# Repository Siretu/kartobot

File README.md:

# kartobot

### Introduction
This project was created by [@Siretu](https://github.com/user/Siretu), [@setfal](https://github.com/user/setfal) and [@exuvo](https://github.com/user/exuvo) as a project course. We built and programmed a navigation robot pretty much from scratch. The robot (called kartobot) is equipped with a tower of two rotating ultrasonic sensors. These rotate continuously to provide the robot with sensor input about its surroundings. This data is then sent to the computer wirelessly using the xbee chip. The navigation data is drawn as a map on the computer and it's also used locally on the robot to avoid obstacles. The robot uses a dynamic A* pathfinding to automatically explore more of the surrounding areas.

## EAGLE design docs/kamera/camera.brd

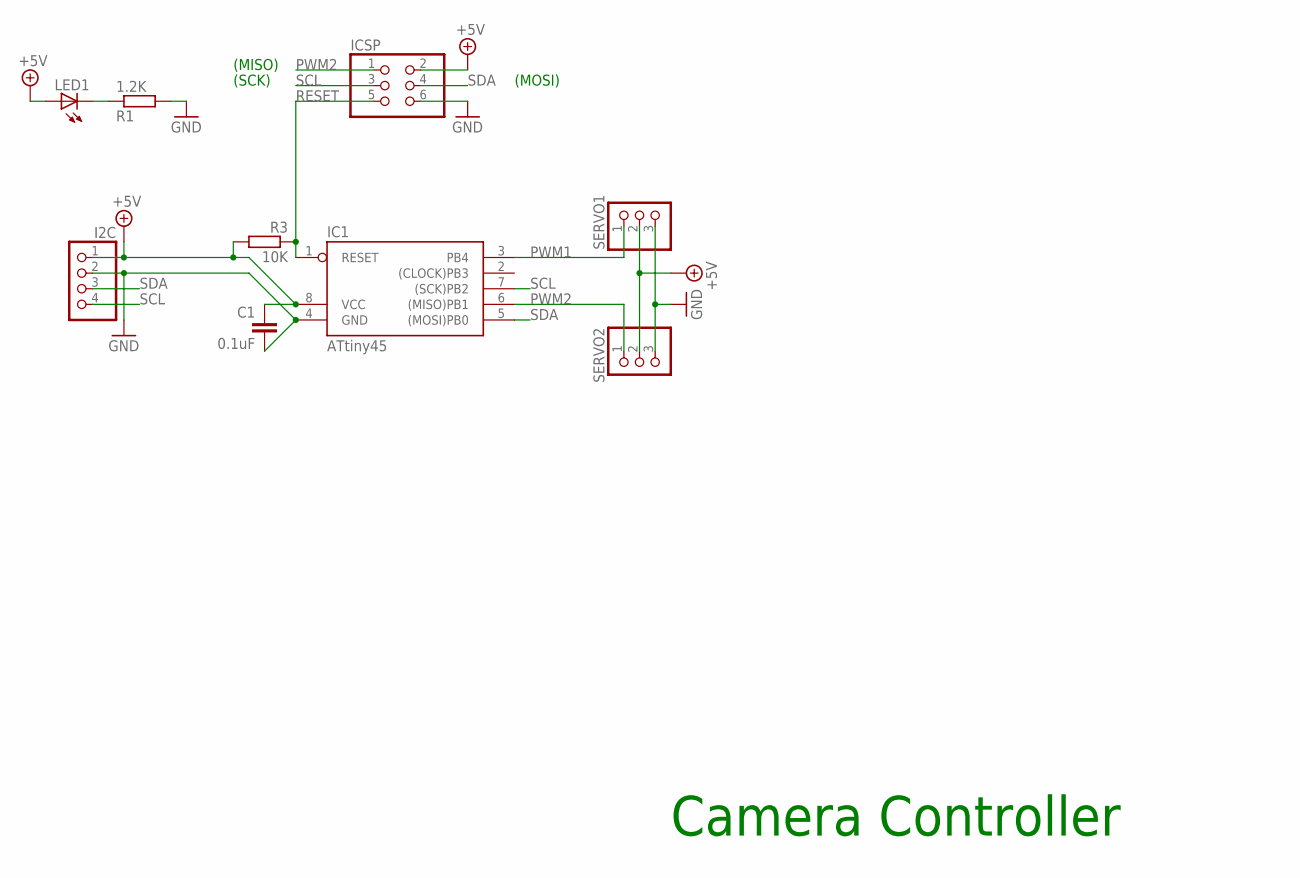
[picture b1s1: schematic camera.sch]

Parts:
C1: 0.1uF; C025-024X044
I2C: PINHD-1X4; 1X04
IC1: ATtiny45; DIL08
ICSP: PINHD-2X3; 2X03
LED1: LED5MM
R1: 1.2K; 0207/2V
R3: 10K; 0207/2V
SERVO1, SERVO2: PINHD-1X3; 1X03

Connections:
+5V: C1.1, I2C.1, IC1.8 (VCC), ICSP.2, LED1.A, R3.2, SERVO1.2, SERVO2.2
GND: C1.2, I2C.2, IC1.4 (GND), ICSP.6, R1.2, SERVO1.3, SERVO2.3
unnamed: LED1.K (C), R1.1
PWM1: IC1.3 (PB4), SERVO1.1
PWM2: IC1.6 ((MISO)PB1), ICSP.1, SERVO2.1
RESET: IC1.1 (RESET), ICSP.5, R3.1
SCL: I2C.4, IC1.7 ((SCK)PB2), ICSP.3
SDA: I2C.3, IC1.5 ((MOSI)PB0), ICSP.4

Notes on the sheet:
(SCK)
(MOSI)
(MISO)
Camera Controller

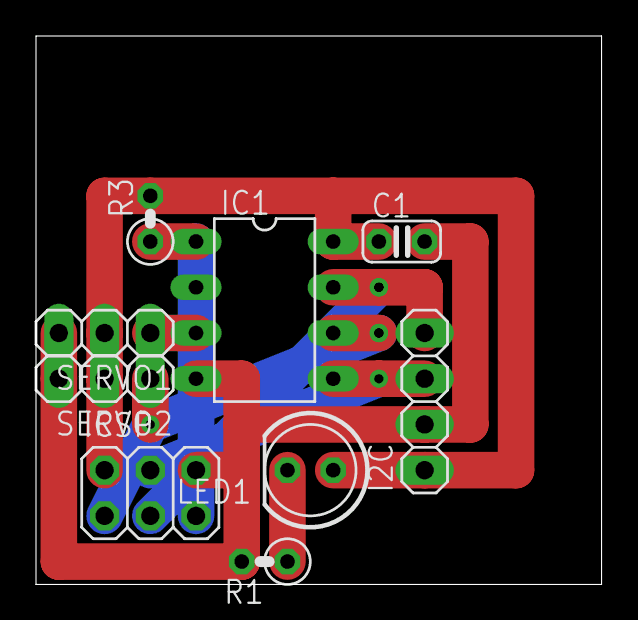
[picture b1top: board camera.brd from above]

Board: 2 copper layers, 31.4 x 30.5 mm, 9 parts (0 on the bottom side), 8 nets.

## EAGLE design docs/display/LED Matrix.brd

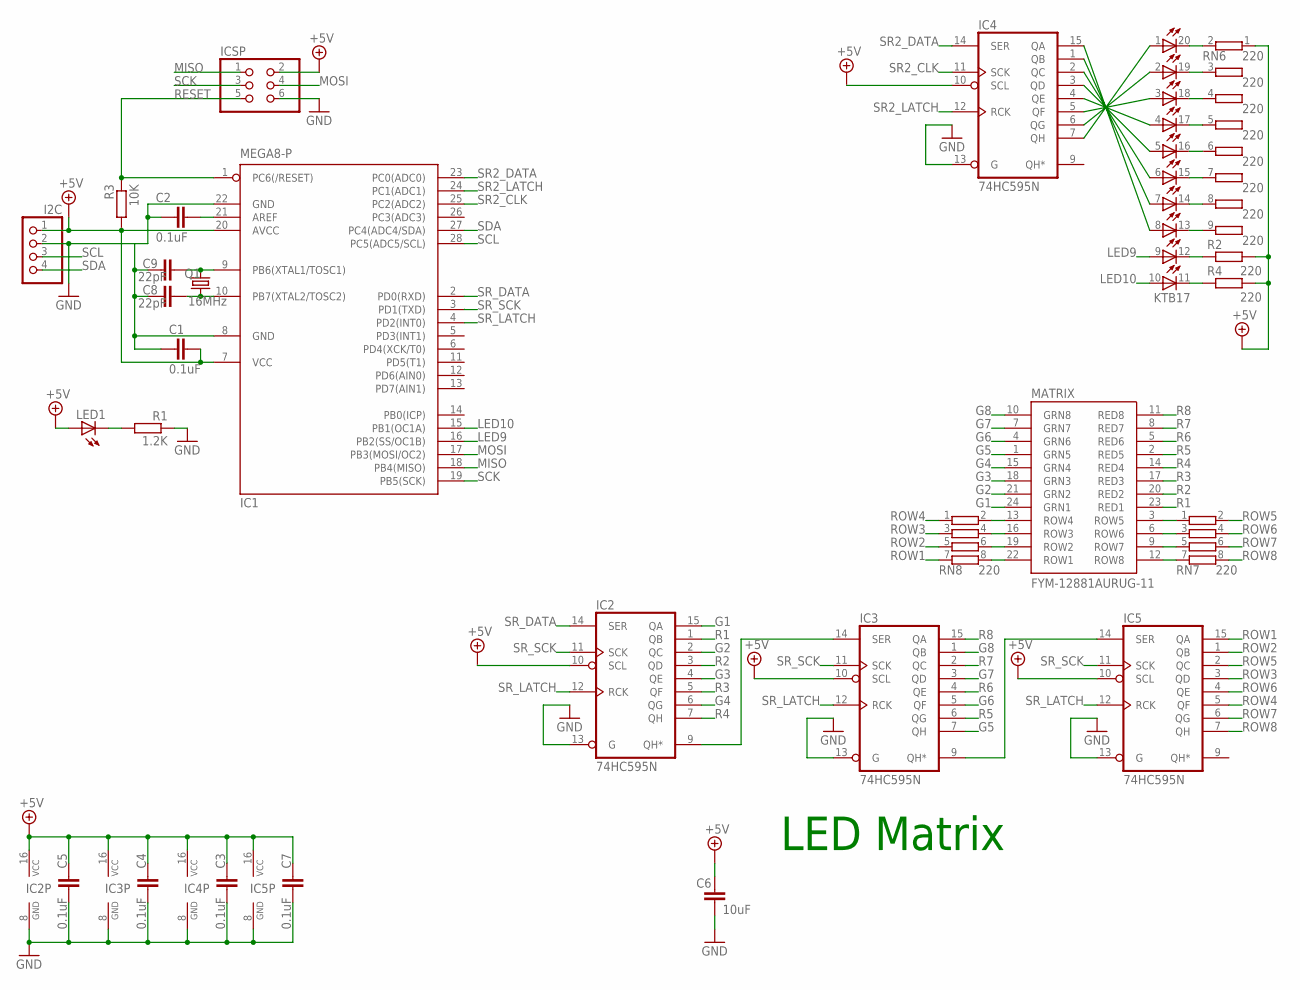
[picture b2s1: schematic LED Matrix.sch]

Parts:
-: KTB17; LB10
C1, C2, C3, C4, C5, C7: 0.1uF; C025-024X044
C6: 10uF; C025-024X044
C8, C9: 22pF; C025-024X044
I2C: PINHD-1X4; 1X04
IC1: MEGA8-P; DIL28-3
IC2, IC3, IC4, IC5: 74HC595N; DIL16
ICSP: PINHD-2X3; 2X03
LED1: LED5MM
MATRIX: FYM-12881AURUG-11; YSM-1288CR3G2C
Q1: 16MHz; HC49/S
R1: 1.2K; 0207/2V
R2, R4: 220; 0207/2V
R3: 10K; 0207/2V
RN6: 220; SIL9
RN7, RN8: 220; SIL8

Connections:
+5V: C1.2, C3.1, C4.1, C5.1, C6.1, C7.1, I2C.1, IC1.7 (VCC), IC1.20 (AVCC), IC2.10 (SCL), IC2.16 (VCC), IC3.10 (SCL), IC3.16 (VCC), IC4.10 (SCL), IC4.16 (VCC), IC5.10 (SCL), IC5.16 (VCC), ICSP.2, LED1.A, R2.2, R3.2, R4.2, RN6.1
G1: IC2.15 (QA), MATRIX.24 (GRN1)
G2: IC2.2 (QC), MATRIX.21 (GRN2)
G3: IC2.4 (QE), MATRIX.18 (GRN3)
G4: IC2.6 (QG), MATRIX.15 (GRN4)
G5: IC3.7 (QH), MATRIX.1 (GRN5)
G6: IC3.5 (QF), MATRIX.4 (GRN6)
G7: IC3.3 (QD), MATRIX.7 (GRN7)
G8: IC3.1 (QB), MATRIX.10 (GRN8)
GND: C1.1, C2.1, C3.2, C4.2, C5.2, C6.2, C7.2, C8.1, C9.1, I2C.2, IC1.8 (GND), IC1.22 (GND), IC2.8 (GND), IC2.13 (G), IC3.8 (GND), IC3.13 (G), IC4.8 (GND), IC4.13 (G), IC5.8 (GND), IC5.13 (G), ICSP.6, R1.1
LED9: -.9 (A), IC1.16 (PB2(SS/OC1B))
LED10: -.10 (A), IC1.15 (PB1(OC1A))
MISO: IC1.18 (PB4(MISO)), ICSP.1
MOSI: IC1.17 (PB3(MOSI/OC2)), ICSP.4
unnamed: LED1.K (C), R1.2
unnamed: -.1 (A), IC4.7 (QH)
unnamed: -.11 (C), R4.1
unnamed: -.12 (C), R2.1
unnamed: -.13 (C), RN6.9 (2)
unnamed: -.14 (C), RN6.8 (2)
unnamed: -.15 (C), RN6.7 (2)
unnamed: -.16 (C), RN6.6 (2)
unnamed: -.17 (C), RN6.5 (2)
unnamed: -.18 (C), RN6.4 (2)
unnamed: -.19 (C), RN6.3 (2)
unnamed: -.20 (C), RN6.2
unnamed: -.2 (A), IC4.6 (QG)
unnamed: -.3 (A), IC4.5 (QF)
unnamed: -.4 (A), IC4.4 (QE)
unnamed: -.5 (A), IC4.3 (QD)
unnamed: -.6 (A), IC4.2 (QC)
unnamed: -.7 (A), IC4.1 (QB)
unnamed: -.8 (A), IC4.15 (QA)
unnamed: C9.2, IC1.9 (PB6(XTAL1/TOSC1)), Q1.2
unnamed: C2.2, IC1.21 (AREF)
unnamed: IC3.9 (QH*), IC5.14 (SER)
unnamed: C8.2, IC1.10 (PB7(XTAL2/TOSC2)), Q1.1
unnamed: IC2.9 (QH*), IC3.14 (SER)
unnamed: MATRIX.13 (ROW4), RN8.2
unnamed: MATRIX.16 (ROW3), RN8.4 (2)
unnamed: MATRIX.19 (ROW2), RN8.6 (2)
unnamed: MATRIX.22 (ROW1), RN8.8 (2)
unnamed: MATRIX.3 (ROW5), RN7.1
unnamed: MATRIX.6 (ROW6), RN7.3 (1)
unnamed: MATRIX.9 (ROW7), RN7.5 (1)
unnamed: MATRIX.12 (ROW8), RN7.7 (1)
R1: IC2.1 (QB), MATRIX.23 (RED1)
R2: IC2.3 (QD), MATRIX.20 (RED2)
R3: IC2.5 (QF), MATRIX.17 (RED3)
R4: IC2.7 (QH), MATRIX.14 (RED4)
R5: IC3.6 (QG), MATRIX.2 (RED5)
R6: IC3.4 (QE), MATRIX.5 (RED6)
R7: IC3.2 (QC), MATRIX.8 (RED7)
R8: IC3.15 (QA), MATRIX.11 (RED8)
RESET: IC1.1 (PC6(/RESET)), ICSP.5, R3.1
ROW1: IC5.15 (QA), RN8.7 (1)
ROW2: IC5.1 (QB), RN8.5 (1)
ROW3: IC5.3 (QD), RN8.3 (1)
ROW4: IC5.5 (QF), RN8.1
ROW5: IC5.2 (QC), RN7.2
ROW6: IC5.4 (QE), RN7.4 (2)
ROW7: IC5.6 (QG), RN7.6 (2)
ROW8: IC5.7 (QH), RN7.8 (2)
SCK: IC1.19 (PB5(SCK)), ICSP.3
SCL: I2C.3, IC1.28 (PC5(ADC5/SCL))
SDA: I2C.4, IC1.27 (PC4(ADC4/SDA))
SR2_CLK: IC1.25 (PC2(ADC2)), IC4.11 (SCK)
SR2_DATA: IC1.23 (PC0(ADC0)), IC4.14 (SER)
SR2_LATCH: IC1.24 (PC1(ADC1)), IC4.12 (RCK)
SR_DATA: IC1.2 (PD0(RXD)), IC2.14 (SER)
SR_LATCH: IC1.4 (PD2(INT0)), IC2.12 (RCK), IC3.12 (RCK), IC5.12 (RCK)
SR_SCK: IC1.3 (PD1(TXD)), IC2.11 (SCK), IC3.11 (SCK), IC5.11 (SCK)

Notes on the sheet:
LED Matrix

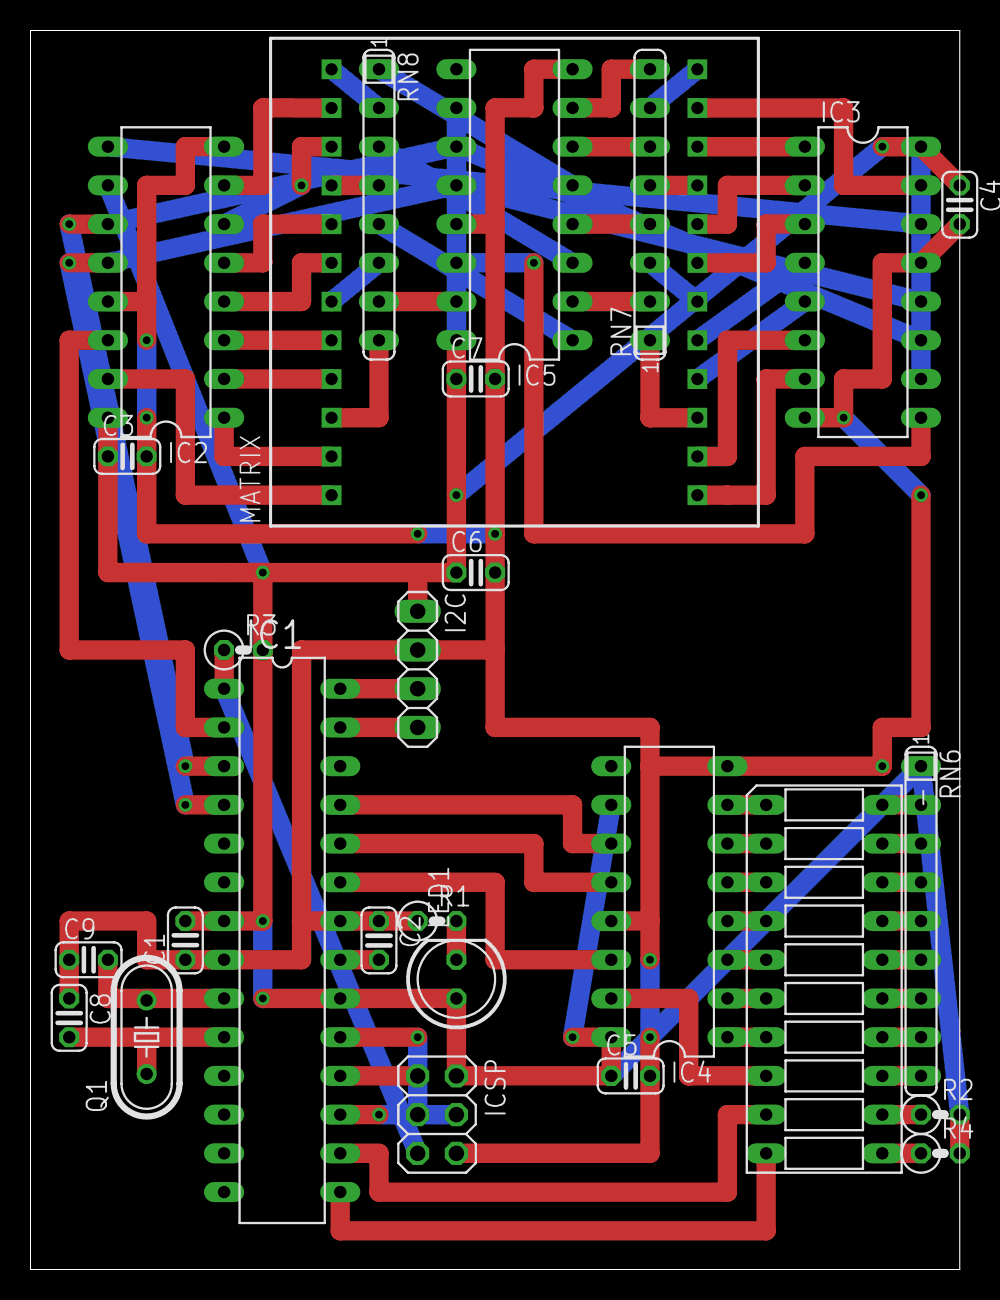
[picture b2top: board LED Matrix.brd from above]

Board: 2 copper layers, 61.0 x 81.3 mm, 27 parts (0 on the bottom side), 72 nets.

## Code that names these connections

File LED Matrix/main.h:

/*
 * quad.h
 *
 *  Created on: 19 Jul 2011
 *      Author: exuvo
 *
 * ---------------------------------------------------------------------
 *  ATMega8
 * ---------------------------------------------------------------------
 *  Fuse lock byte
 *  0x2f = - - 1 1   1 1 1 1
 *             \ /   \ / \ /
 *              |     |   +----- LB 2..1 (11 = No memory lock)
 *              |     +------------ BLB0 02..01 (11 = no restrictions in Application section.)
 *              +------------ BLB1 12..11 (11 = no restrictions in Boot Loader section.)
 *  Fuse high byte:
 *  0xc7 = 1 1 0 0   0 1 1 1 <-- BOOTRST (1 = jump to application at start)
 *         ^ ^ ^ ^   ^ \ /
 *         | | | |   |  +------- BOOTSZ 0..1 (11 = 256B starting at 0xF80)
 *         | | | |   + --------- EESAVE (0 = preserve EEPROM over chip erase)
 *         | | | +-------------- CKOPT (0 = high frequency oscillator)
 *         | | +---------------- SPIEN (0 = allow serial programming)
 *         | +------------------ WDTON (1 = watchdog disabled at start)
 *         +-------------------- RSTDISBL (1 = reset pin is enabled)
 *  Fuse low byte:
 *  0x2f = 0 0 1 0   1 1 1 1
 *         ^ ^ \ /   \--+--/
 *         | |  |       +------- CKSEL 3..0 (1111 = crystal oscillator)
 *         | |  +--------------- SUT 1..0 (10 = startup time 16K CK + 4.1ms)
 *         | +------------------ BODEN (0 = Brown out detector enabled)
 *         +-------------------- BODLEVEL (0 = brown out @ 4V)
 *                  _____                            _____  _____
 *                  RESET -      (PCINT14/RESET) PC6|1    \/   28|PC5 (ADC5/SCL/PCINT13) - I2C SCL
 *        MATRIX_SR_DATA  -        (PCINT16/RXD) PD0|2         27|PC4 (ADC4/SDA/PCINT12) - I2C SDA
 *        MATRIX_SR_SCK   -        (PCINT17/TXD) PD1|3  ATmega 26|PC3 (ADC3/PCINT11)     -
 *        MATRIX_SR_LATCH -       (PCINT18/INT0) PD2|4     8   25|PC2 (ADC2/PCINT10)     - BAR_SR_CLK
 *                        -  (PCINT19/OC2B/INT1) PD3|5         24|PC1 (ADC1/PCINT9)      - BAR_SR_LATCH
 *                        -     (PCINT20/XCK/T0) PD4|6         23|PC0 (ADC0/PCINT8)      - BAR_SR_DATA
 *                     5V -                      VCC|7         22|GND                    - 0V
 *                     0V -                      GND|8         21|AREF                   - 0.1uF - GND
 *                  16MHz - (PCINT6/XTAL1/TOSC1) PB6|9         20|AVCC                   - 5V
 *                  16MHz - (PCINT7/XTAL2/TOSC2) PB7|10        19|PB5 (SCK/PCINT5)       - SCK
 *                        -    (PCINT21/OC0B/T1) PD5|11        18|PB4 (MISO/PCINT4)      - MISO
 *                        -  (PCINT22/OC0A/AIN0) PD6|12        17|PB3 (MOSI/OC2A/PCINT3) - MOSI
 *                        -       (PCINT23/AIN1) PD7|13        16|PB2 (SS/OC1B/PCINT2)   - BAR_9
 *                        -   (PCINT0/CLKO/ICP1) PB0|14        15|PB1 (OC1A/PCINT1)      - BAR_10
 *                                                  |____________|
 *
 *
 *
 *
 *
 *	I2C Address list:
 *	Ourselves	0x1		1
 *
 *	Timers:
 *	0: time
 *	1: PWM
 *	2: PWM
 *
 */

#ifndef MAIN_H_
#define MAIN_H_

#include "utils.h"

#include <Print.h>
#include <Streaming/Streaming.h>
#include "time.h"
#include <SimpleTimer/SimpleTimer.h>

extern uint16_t load;
extern SimpleTimer timer;

//Dynamic memory allocation
void * operator new(size_t size);
void * operator new[](size_t size);
void operator delete(void * ptr);
void operator delete[](void * ptr);
__extension__ typedef int __guard __attribute__((mode (__DI__)));
extern "C" int __cxa_guard_acquire(__guard *);
extern "C" void __cxa_guard_release (__guard *);
extern "C" void __cxa_guard_abort (__guard *);
extern "C" void __cxa_pure_virtual(void);

#endif

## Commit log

2015-01-27 Update README.md
    Added links to authors
